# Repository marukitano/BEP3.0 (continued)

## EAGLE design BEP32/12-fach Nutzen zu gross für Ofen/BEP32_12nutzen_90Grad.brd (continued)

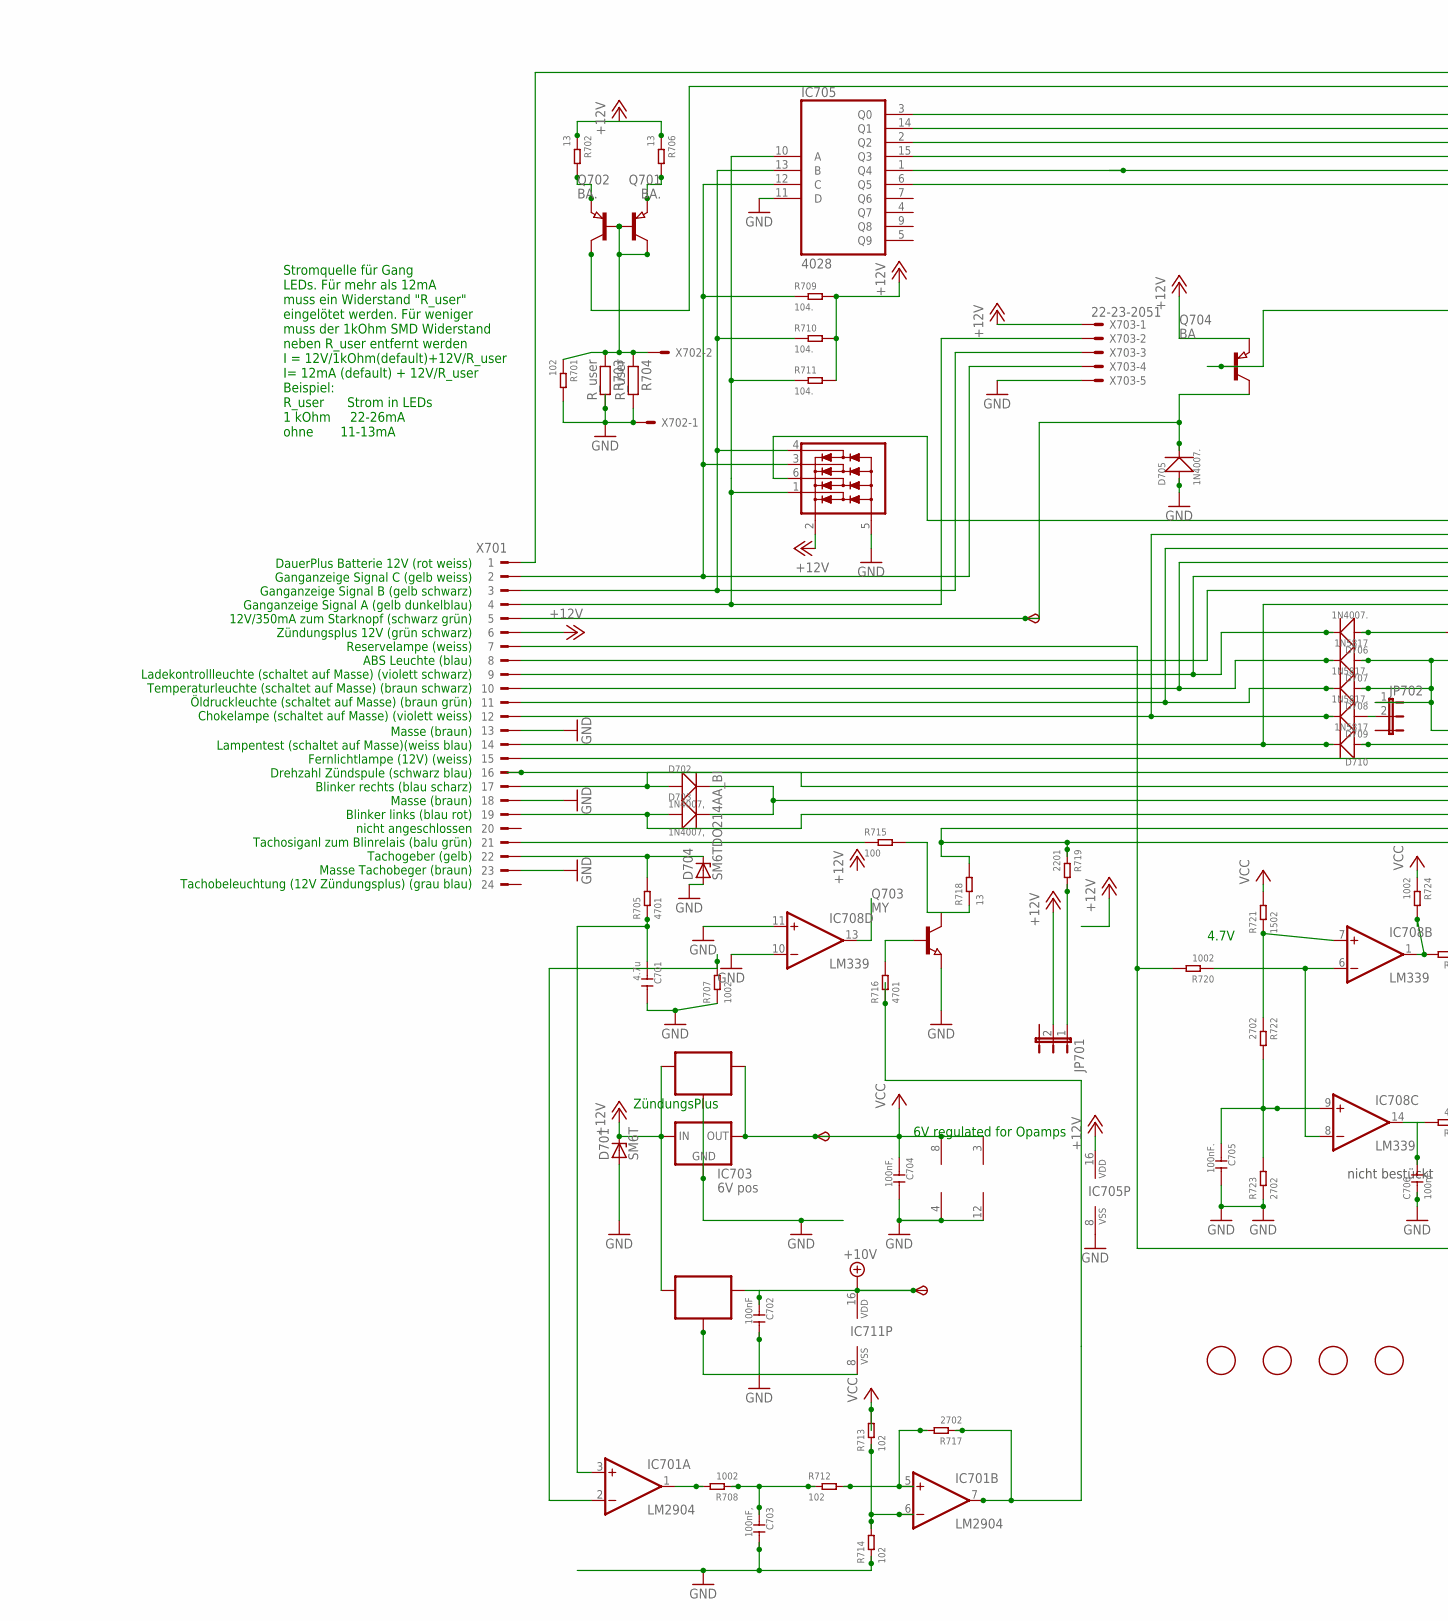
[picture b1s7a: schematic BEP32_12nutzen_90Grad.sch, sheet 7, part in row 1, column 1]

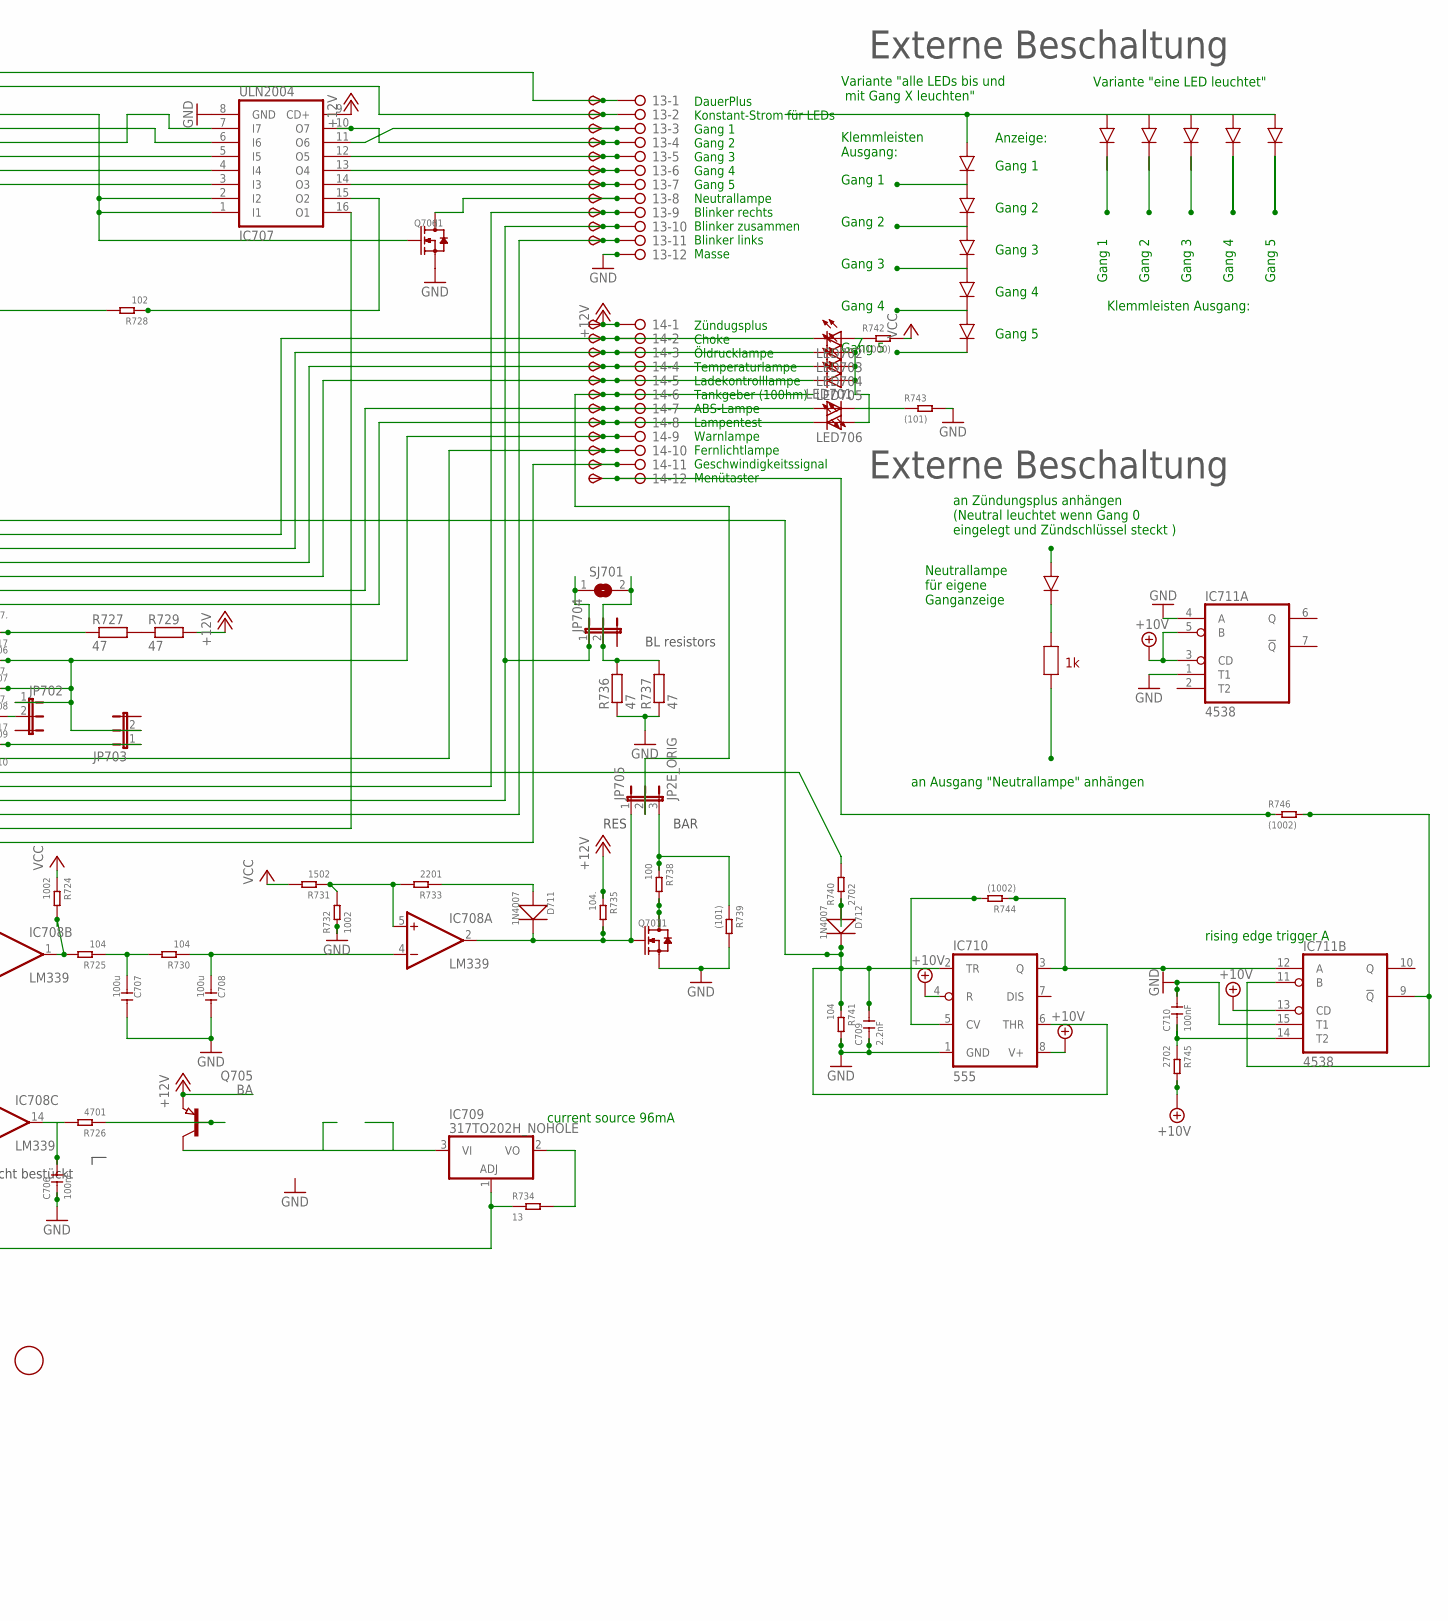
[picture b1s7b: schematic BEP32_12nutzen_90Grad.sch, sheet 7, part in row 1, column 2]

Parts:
6V701, 10V701: TPSB2.0; B2.0
13, 14: 2081-1132; 12-PIN
C701: 4.7u; C0805
C702, C710: 100nF; C0805
C703, C704: 100nF,; C0805
C705, C706: 100nF.; C0805
C707, C708: 100u; C1206
C709: 2.2nF; C0805
D701: SM6T; DO214AA
D702, D703: 1N4007,; DO-214AC
D704: SM6TDO214AA_BI; DO214AA_BI
D705, D706: 1N4007.; DO-214AC
D707, D710: 1N5817; DO-214AC_SLIM
D708, D709: 1N5817.; DO-214AC_SLIM
D711, D712: 1N4007; DO-214AC
FID701, FID702, FID703, FID704: FIDUCIAL; FIDUCIAL_1MM
IC701: LM2904; SO08
IC702: 78L06; SOT89_ROUND
IC703: 6V pos; 78LXX
IC704: 78L10; SOT89_ROUND
IC705: 4028; SO16
IC706: NUP4304SOT457_R; SOT457R_PHILIPS
IC707: ULN2004; SO16
IC708: LM339; SO14
IC709: 317TO202H_NOHOLE; TO220H_NOHOLE
IC710: 555; SO08
IC711: 4538; SO16
JP701, JP702, JP703, JP704: JP2EJP2_SMALLPADS; JP2_SMALLPADS
JP705: JP2E_ORIG; JP2_ORIG_SMALLPADS
LED701, LED702, LED703, LED704, LED705, LED706: LEDLD260; LD260
Q701, Q702: BA.; SOT89
Q703: MY; SOT89
Q704, Q705: BA; SOT89
Q706, Q707: J1; SOT-23
R701, R712, R713, R714, R728: 102; R0805
R702, R706, R718, R734: 13; R1206
R703, R704: R_user; R0805
R705, R716, R726: 4701; R0805
R707, R708, R720, R724, R732: 1002; R0805
R709, R710, R711, R735: 104.; R0805
R715, R738: 100; R0805
R717, R722, R723, R740, R745: 2702; R0805
R719, R733: 2201; R0805
R721, R731: 1502; R0805
R725, R730, R741: 104; R0805
R727, R729, R736, R737: 47; V235/17_1MM
R739, R743: (101); R0805
R742: (1000); R0805
R744, R746: (1002); R0805
SJ701: SJ
START701: TPSB2.0; B2.0
TP139, TP140, TP141, TP142, TP143, TP144, TP145, TP146, TP147, TP148, TP149, TP150, TP151, TP152, TP153, TP154, TP155, TP156, TP158, TP159, TP160, TP161: TPSB2.0; B2.0
TP157: TPSB1,27; B1,27
X701: CON_BMWV2; 24-PIN_V2
X702: 22-23-2021
X703: 22-23-2051

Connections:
+10V: 10V701.TP, C702.1, IC704.1 (OUT), IC710.4 (R), IC710.8 (V+), IC711.3 (CD), IC711.5 (B), IC711.13 (CD), IC711.16 (VDD), R745.2; also elsewhere on the board
+12V: 14.1, D701.C, IC702.3 (IN), IC703.IN, IC704.3 (IN), IC705.16 (VDD), IC706.2 (V+), IC707.9 (CD+), JP701.2, Q704.3 (E), Q705.3 (E), R702.1, R706.1, R709.2, R710.2, R711.2, R729.2, R735.1, TP160.TP, X701.6, X703.1; also elsewhere on the board
+12V7: IC701.7 (OUT), R716.1, R717.1
GND: 13.12, C701.2, C702.2, C703.2, C704.2, C705.2, C706.1, C707.2, C708.2, C709.1, C710.2, D701.A, D704.A, D705.1 (+), IC701.4 (V-), IC702.2 (GND), IC702.2@1 (GND), IC703.GND, IC704.2 (GND), IC704.2@1 (GND), IC705.8 (VSS), IC705.11 (D), IC706.5 (V-), IC707.8 (GND), IC708.10 (-IN), IC708.11 (+IN), IC708.12 (GND), IC710.1 (GND), IC711.1 (T1), IC711.4 (A), IC711.8 (VSS), IC711.15 (T1), Q703.3 (E), Q706.2 (S), Q707.2 (S), R701.2, R703.2, R704.2, R707.1, R714.1, R723.1, R732.1, R736.1, R737.1, R739.2, R741.2, R743.2, X701.13, X701.18, X701.23, X702.1, X703.5; also elsewhere on the board
unnamed: R727.2, R729.1
unnamed: 14.9, D707.1 (+), D708.1 (+), JP702.1, JP703.2, TP157.TP
unnamed: IC705.10 (A), IC706.1 (D1), R711.1, X701.4, X703.2
unnamed: IC705.13 (B), IC706.4 (D4), R710.1, X701.3, X703.3
unnamed: D705.2 (-), Q704.2 (C), START701.TP, X701.5
unnamed: IC705.12 (C), IC706.3 (D3), R709.1, X701.2, X703.4
unnamed: 14.7, LED701.A, TP155.TP, X701.8
unnamed: 14.2, D709.2 (-), LED702.K (C), TP150.TP, X701.12
unnamed: 14.3, D708.2 (-), LED703.K (C), TP151.TP, X701.11
unnamed: 14.4, D707.2 (-), LED704.K (C), TP152.TP, X701.10
unnamed: 14.8, D710.2 (-), LED706.K (C), TP156.TP, X701.14
unnamed: 13.9, D702.1 (+), TP147.TP, X701.17
unnamed: 13.11, D703.1 (+), TP149.TP, X701.19
unnamed: D704.C, R705.2, X701.22
unnamed: C701.1, IC701.3 (+IN), R705.1
unnamed: 14.11, IC707.16 (O1), R718.2, R719.1, TP159.TP
unnamed: IC708.1 (OUT), R724.2, R725.2
unnamed: C707.1, R725.1, R730.2
unnamed: C708.1, IC708.4 (-IN), R730.1
unnamed: IC708.5 (+IN), R731.1, R732.2, R733.2
unnamed: D711.1 (+), R733.1
unnamed: C705.1, IC708.9 (+IN), R722.2, R723.2
unnamed: C706.2, IC708.14 (OUT), R726.2
unnamed: Q705.1 (B), R726.1
unnamed: IC705.2 (Q2), IC707.7 (I7)
unnamed: 13.5, IC707.12 (O5), TP143.TP
unnamed: IC705.1 (Q4), IC707.4 (I4)
unnamed: 13.8, Q706.3 (D), TP146.TP
unnamed: 14.10, TP158.TP, X701.15
unnamed: 14.5, D706.2 (-), LED705.K (C), TP153.TP, X701.9
unnamed: D706.1 (+), R727.1
unnamed: IC705.6 (Q5), IC707.3 (I3)
unnamed: 13.4, IC707.10 (O7), TP142.TP
unnamed: IC709.1 (ADJ), R720.2, R734.1, X701.7
unnamed: IC708.6 (-IN), IC708.8 (-IN), R720.1
unnamed: 13.2, Q701.2 (C), TP140.TP
unnamed: 13.1, TP139.TP, X701.1
unnamed: R740.2, X701.16
unnamed: IC705.15 (Q3), IC707.5 (I5)
unnamed: 13.6, IC707.13 (O4), TP144.TP
unnamed: 13.7, IC707.14 (O3), TP145.TP
unnamed: 14.6, JP705.2, TP154.TP
unnamed: LED701.K (C), R743.1
unnamed: LED702.A, LED703.A, LED704.A, LED705.A, LED706.A, R742.1
unnamed: Q704.1 (B), R728.2
unnamed: IC705.3 (Q0), IC707.1 (I1), IC707.2 (I2), Q706.1 (G)
unnamed: IC705.14 (Q1), IC707.6 (I6)
unnamed: 13.3, IC707.11 (O6), TP141.TP
unnamed: Q701.1 (B), Q702.1 (B), Q702.2 (C), R701.1, R703.1, R704.1, X702.2
unnamed: Q701.3 (E), R702.2
unnamed: Q702.3 (E), R706.2
unnamed: IC708.7 (+IN), R721.1, R722.1
unnamed: IC701.2 (-IN), R707.2
unnamed: Q703.1 (B), R716.2
unnamed: Q707.3 (D), R738.2
unnamed: IC709.2 (VO), R734.2
unnamed: IC709.3 (VI), Q705.2 (C)
unnamed: C709.2, D712.2 (-), IC706.6 (D2), IC710.2 (TR), IC710.6 (THR), R741.1
unnamed: IC710.5 (CV), R744.2
unnamed: IC710.3 (Q), IC711.12 (A), R744.1
unnamed: D712.1 (+), R740.1
unnamed: 13.10, D702.2 (-), D703.2 (-), JP704.1, SJ701.1, TP148.TP
unnamed: JP704.2, R736.2, R737.2, SJ701.2
unnamed: IC711.9 (!Q), IC711.11 (B), R746.2
unnamed: C710.1, IC711.14 (T2), R745.1
unnamed: JP701.1, R719.2
unnamed: IC707.15 (O2), R728.1
unnamed: 14.12, R746.1, TP161.TP
unnamed: D709.1 (+), JP702.2
unnamed: D711.2 (-), IC708.2 (OUT), JP705.1, Q707.1 (G), R735.2
unnamed: IC701.1 (OUT), R708.2
unnamed: C703.1, R708.1, R712.1
unnamed: IC701.5 (+IN), R712.2, R717.2
unnamed: IC701.6 (-IN), R713.1, R714.2
unnamed: D710.1 (+), JP703.1
unnamed: JP705.3, R738.1, R739.1
unnamed: R715.1, X701.21
unnamed: Q703.2 (C), R715.2, R718.1
VCC: 6V701.TP, C704.1, IC701.8 (V+), IC702.1 (OUT), IC703.OUT, IC708.3 (V+), R713.2, R721.2, R724.1, R731.2, R742.2; also elsewhere on the board

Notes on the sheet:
6V regulated for Opamps
current source 96mA
ZündungsPlus
Zündugsplus Choke Öldrucklampe Temperaturlampe Ladekontrolllampe Tankgeber (100hm) ABS-Lampe Lampentest Warnlampe Fernlichtlampe Geschwindigkeitssignal Menütaster
DauerPlus Konstant-Strom für LEDs Gang 1 Gang 2 Gang 3 Gang 4 Gang 5 Neutrallampe Blinker rechts Blinker zusammen Blinker links Masse
DauerPlus Batterie 12V (rot weiss) Ganganzeige Signal C (gelb weiss) Ganganzeige Signal B (gelb schwarz) Ganganzeige Signal A (gelb dunkelblau) 12V/350mA zum Starknopf (schwarz grün) Zündungsplus 12V (grün schwarz) Reservelampe (weiss) ABS Leuchte (blau) Ladekontrollleuchte (schaltet auf Masse) (vi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
Masse (braun) Lampentest (schaltet auf Masse)(weiss blau) Fernlichtlampe (12V) (weiss) Drehzahl Zündspule (schwarz blau) Blinker rechts (blau scharz) Masse (braun) Blinker links (blau rot) nicht angeschlossen Tachosiganl zum Blinrelais (balu grün) Tachogeber (gelb) Masse Tachobeger (braun) Tachobel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
4.7V
Stromquelle für Gang LEDs. Für mehr als 12mA muss ein Widerstand "R_user" eingelötet werden. Für weniger muss der 1kOhm SMD Widerstand neben R_user entfernt werden I = 12V/1kOhm(default)+12V/R_user I= 12mA (default) + 12V/R_user Beispiel: R_user Strom in LEDs 1 kOhm 22-26mA ohne 11-13mA
Gang 1
Gang 2
Gang 3
Gang 4
Gang 5
Variante "eine LED leuchtet"
Variante "alle LEDs bis und mit Gang X leuchten"
Klemmleisten Ausgang:
Klemmleisten Ausgang:
an Zündungsplus anhängen (Neutral leuchtet wenn Gang 0 eingelegt und Zündschlüssel steckt )
an Ausgang "Neutrallampe" anhängen
Neutrallampe für eigene Ganganzeige
Externe Beschaltung
Anzeige:
nicht bestückt
rising edge trigger A
BAR
RES
BL resistors

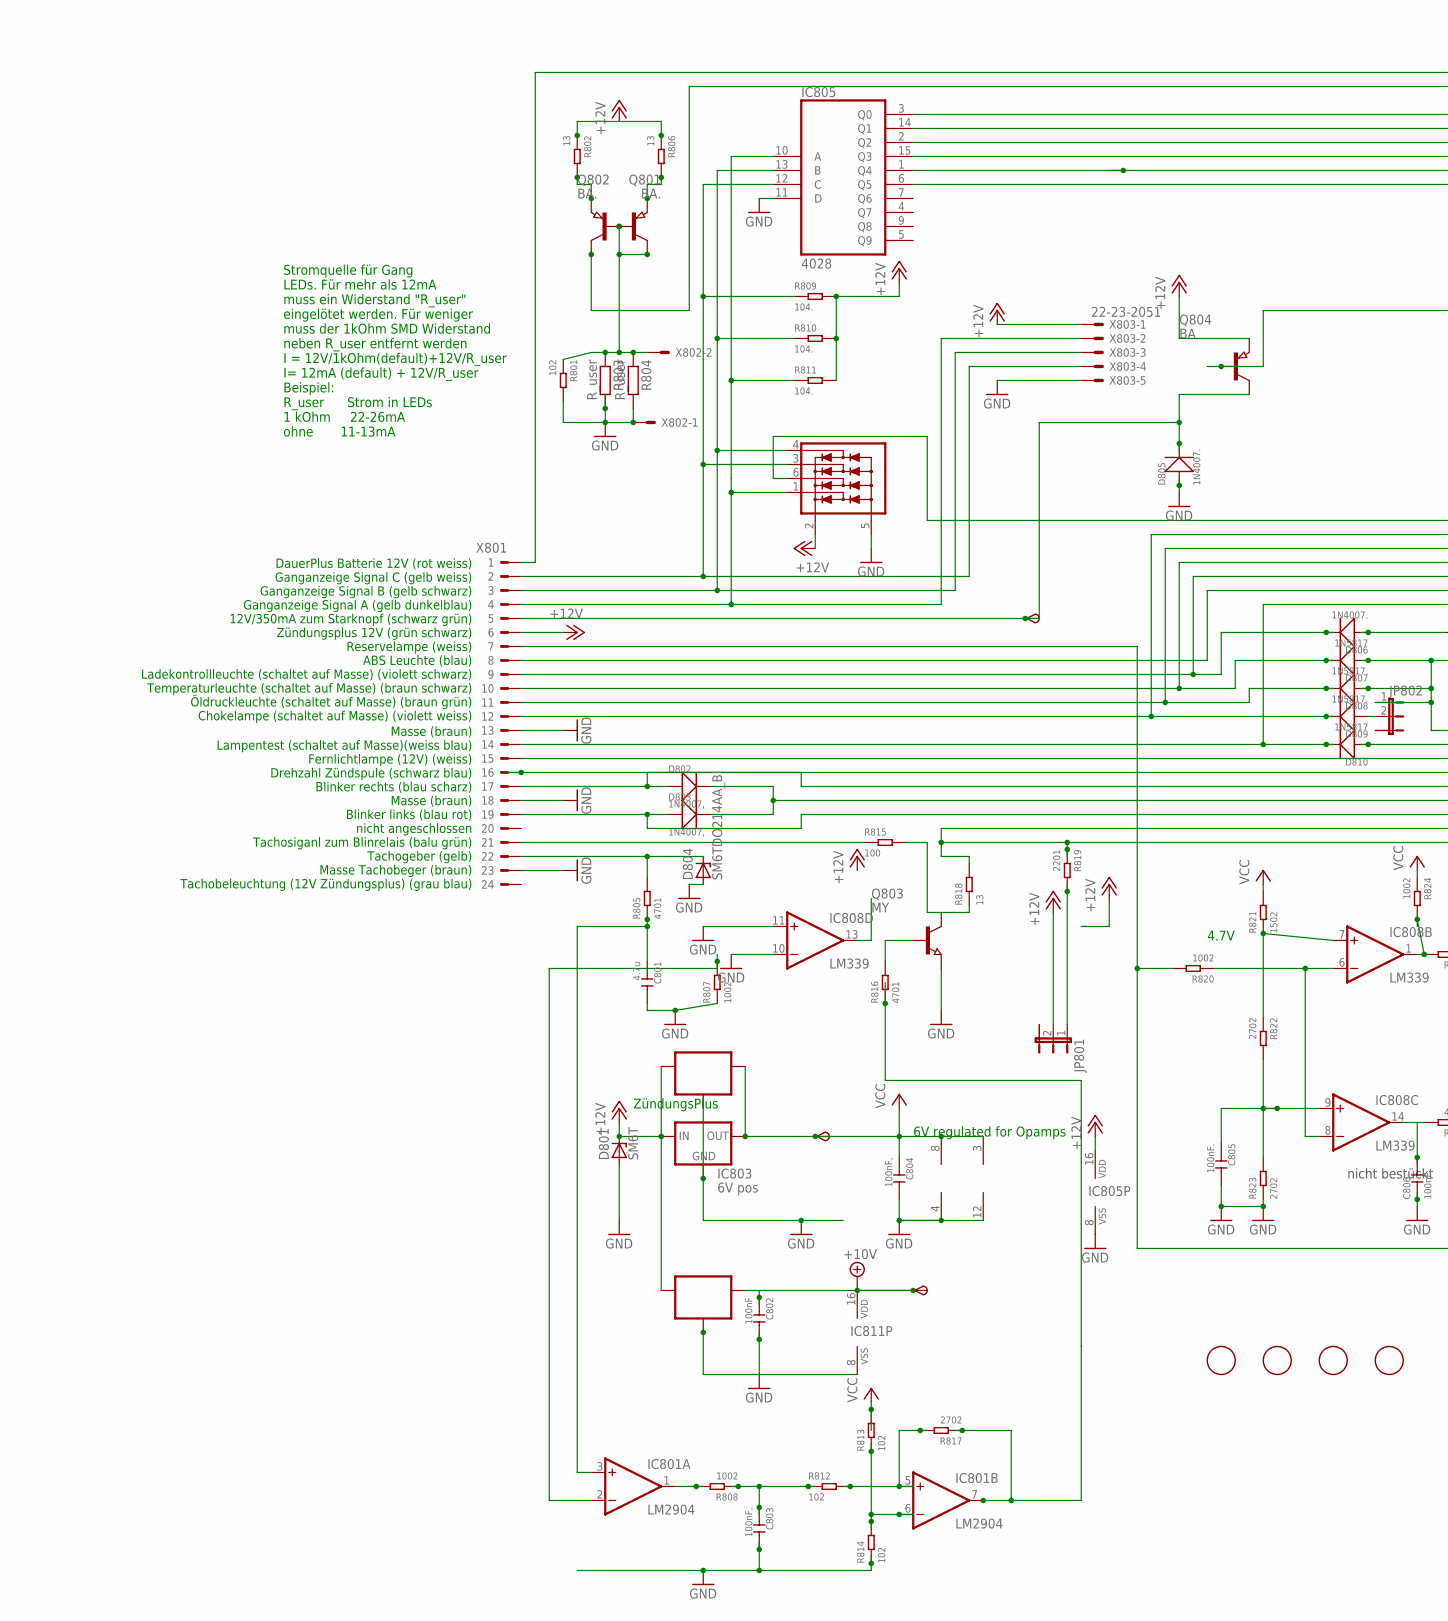
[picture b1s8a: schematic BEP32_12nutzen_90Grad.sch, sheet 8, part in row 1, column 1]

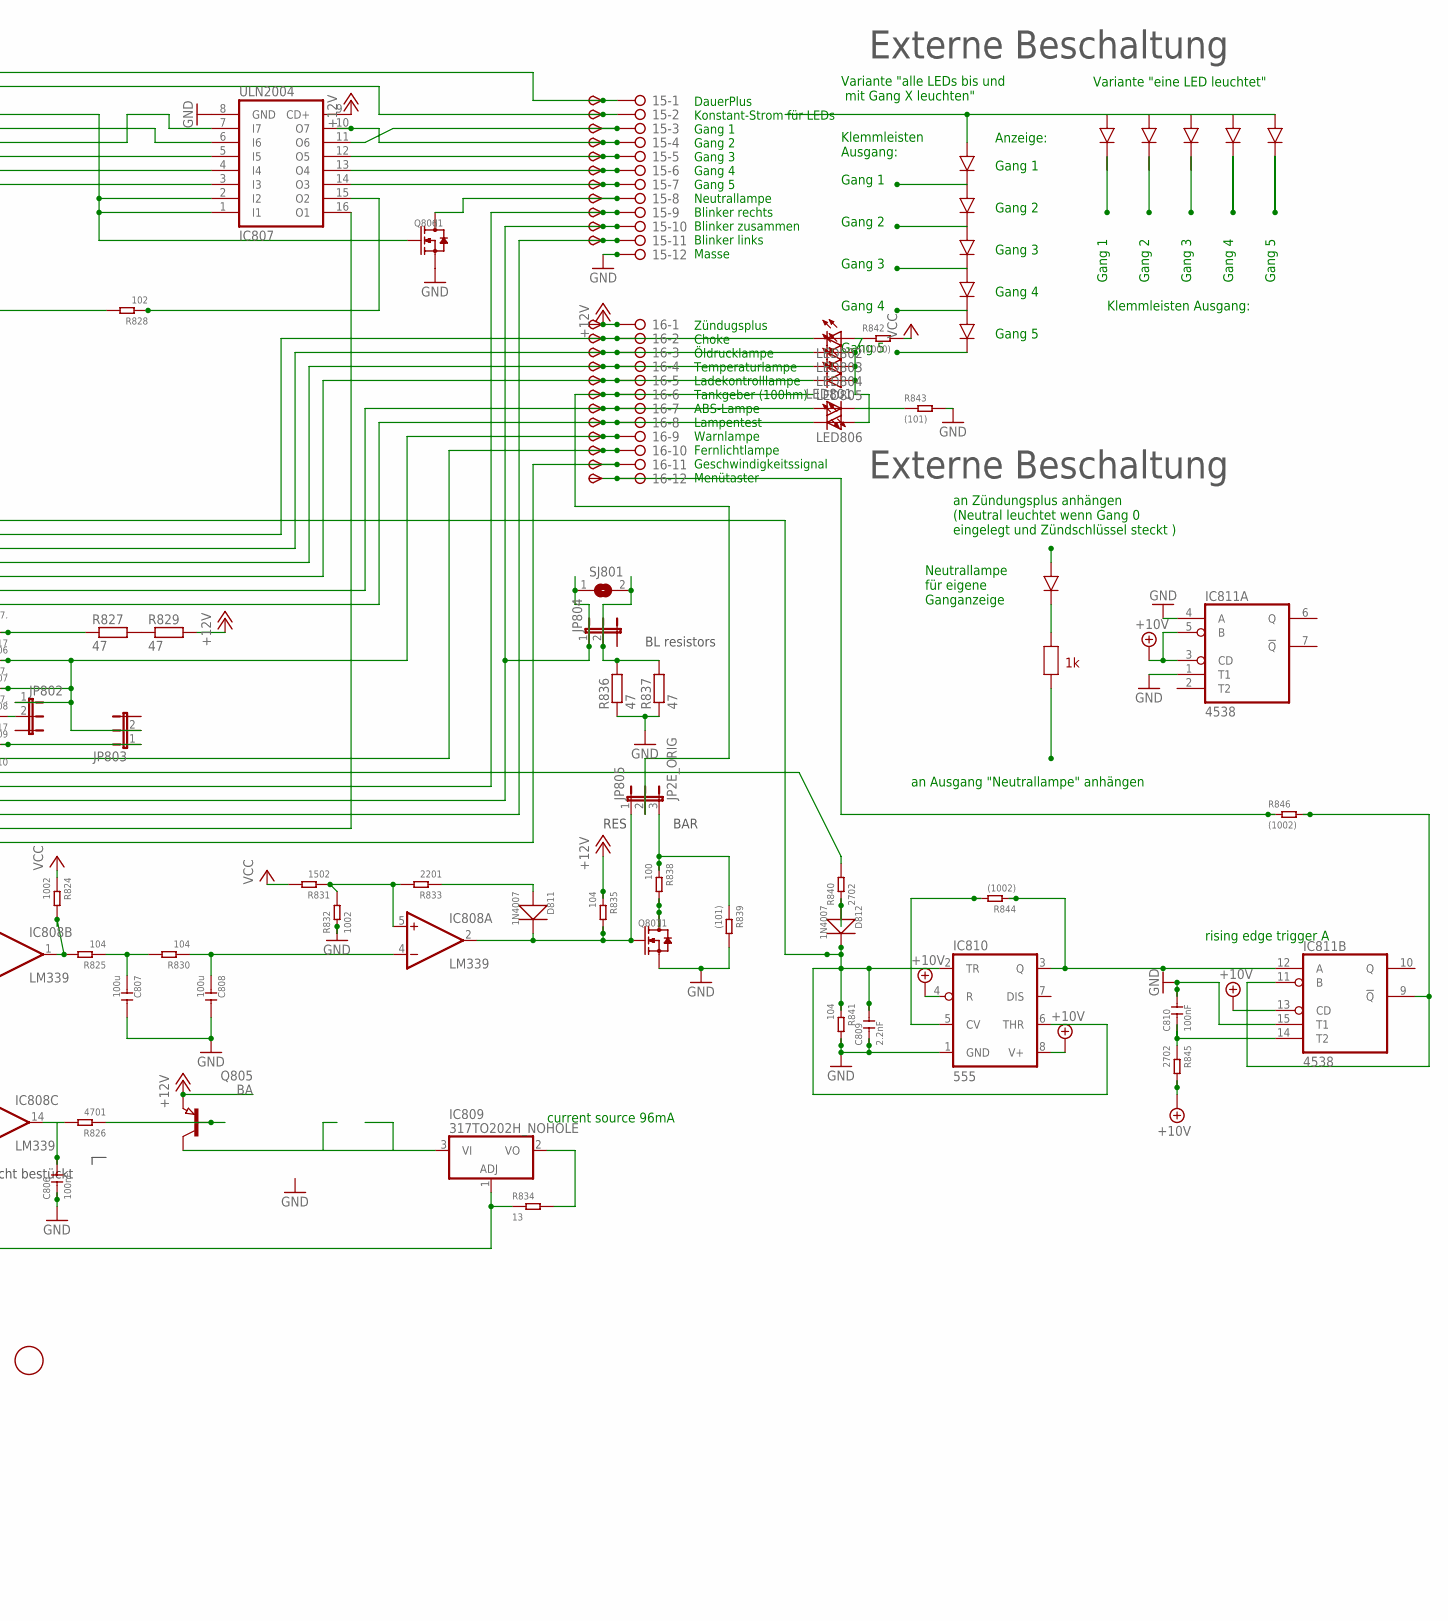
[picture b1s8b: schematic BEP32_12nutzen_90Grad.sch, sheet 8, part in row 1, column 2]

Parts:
6V801, 10V801: TPSB2.0; B2.0
15, 16: 2081-1132; 12-PIN
C801: 4.7u; C0805
C802, C810: 100nF; C0805
C803, C804: 100nF,; C0805
C805, C806: 100nF.; C0805
C807, C808: 100u; C1206
C809: 2.2nF; C0805
D801: SM6T; DO214AA
D802, D803: 1N4007,; DO-214AC
D804: SM6TDO214AA_BI; DO214AA_BI
D805, D806: 1N4007.; DO-214AC
D807, D810: 1N5817; DO-214AC_SLIM
D808, D809: 1N5817.; DO-214AC_SLIM
D811, D812: 1N4007; DO-214AC
FID801, FID802, FID803, FID804: FIDUCIAL; FIDUCIAL_1MM
IC801: LM2904; SO08
IC802: 78L06; SOT89_ROUND
IC803: 6V pos; 78LXX
IC804: 78L10; SOT89_ROUND
IC805: 4028; SO16
IC806: NUP4304SOT457_R; SOT457R_PHILIPS
IC807: ULN2004; SO16
IC808: LM339; SO14
IC809: 317TO202H_NOHOLE; TO220H_NOHOLE
IC810: 555; SO08
IC811: 4538; SO16
JP801, JP802, JP803, JP804: JP2EJP2_SMALLPADS; JP2_SMALLPADS
JP805: JP2E_ORIG; JP2_ORIG_SMALLPADS
LED801, LED802, LED803, LED804, LED805, LED806: LEDLD260; LD260
Q801, Q802: BA.; SOT89
Q803: MY; SOT89
Q804, Q805: BA; SOT89
Q806, Q807: J1; SOT-23
R801, R812, R813, R814, R828: 102; R0805
R802, R806, R818, R834: 13; R1206
R803, R804: R_user; R0805
R805, R816, R826: 4701; R0805
R807, R808, R820, R824, R832: 1002; R0805
R809, R810, R811: 104.; R0805
R815, R838: 100; R0805
R817, R822, R823, R840, R845: 2702; R0805
R819, R833: 2201; R0805
R821, R831: 1502; R0805
R825, R830, R835, R841: 104; R0805
R827, R829, R836, R837: 47; V235/17_1MM
R839, R843: (101); R0805
R842: (1000); R0805
R844, R846: (1002); R0805
SJ801: SJ
START801: TPSB2.0; B2.0
TP162, TP163, TP164, TP165, TP166, TP167, TP168, TP169, TP170, TP171, TP172, TP173, TP174, TP175, TP176, TP177, TP178, TP179, TP181, TP182, TP183, TP184: TPSB2.0; B2.0
TP180: TPSB1,27; B1,27
X801: CON_BMWV2; 24-PIN_V2
X802: 22-23-2021
X803: 22-23-2051

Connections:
+10V: 10V801.TP, C802.1, IC804.1 (OUT), IC810.4 (R), IC810.8 (V+), IC811.3 (CD), IC811.5 (B), IC811.13 (CD), IC811.16 (VDD), R845.2; also elsewhere on the board
+12V: 16.1, D801.C, IC802.3 (IN), IC803.IN, IC804.3 (IN), IC805.16 (VDD), IC806.2 (V+), IC807.9 (CD+), JP801.2, Q804.3 (E), Q805.3 (E), R802.1, R806.1, R809.2, R810.2, R811.2, R829.2, R835.1, TP183.TP, X801.6, X803.1; also elsewhere on the board
+12V8: IC801.7 (OUT), R816.1, R817.1
GND: 15.12, C801.2, C802.2, C803.2, C804.2, C805.2, C806.1, C807.2, C808.2, C809.1, C810.2, D801.A, D804.A, D805.1 (+), IC801.4 (V-), IC802.2 (GND), IC802.2@1 (GND), IC803.GND, IC804.2 (GND), IC804.2@1 (GND), IC805.8 (VSS), IC805.11 (D), IC806.5 (V-), IC807.8 (GND), IC808.10 (-IN), IC808.11 (+IN), IC808.12 (GND), IC810.1 (GND), IC811.1 (T1), IC811.4 (A), IC811.8 (VSS), IC811.15 (T1), Q803.3 (E), Q806.2 (S), Q807.2 (S), R801.2, R803.2, R804.2, R807.1, R814.1, R823.1, R832.1, R836.1, R837.1, R839.2, R841.2, R843.2, X801.13, X801.18, X801.23, X802.1, X803.5; also elsewhere on the board
unnamed: R827.2, R829.1
unnamed: 16.9, D807.1 (+), D808.1 (+), JP802.1, JP803.2, TP180.TP
unnamed: IC805.10 (A), IC806.1 (D1), R811.1, X801.4, X803.2
unnamed: IC805.13 (B), IC806.4 (D4), R810.1, X801.3, X803.3
unnamed: D805.2 (-), Q804.2 (C), START801.TP, X801.5
unnamed: IC805.12 (C), IC806.3 (D3), R809.1, X801.2, X803.4
unnamed: 16.7, LED801.A, TP178.TP, X801.8
unnamed: 16.2, D809.2 (-), LED802.K (C), TP173.TP, X801.12
unnamed: 16.3, D808.2 (-), LED803.K (C), TP174.TP, X801.11
unnamed: 16.4, D807.2 (-), LED804.K (C), TP175.TP, X801.10
unnamed: 16.8, D810.2 (-), LED806.K (C), TP179.TP, X801.14
unnamed: 15.9, D802.1 (+), TP170.TP, X801.17
unnamed: 15.11, D803.1 (+), TP172.TP, X801.19
unnamed: D804.C, R805.2, X801.22
unnamed: C801.1, IC801.3 (+IN), R805.1
unnamed: 16.11, IC807.16 (O1), R818.2, R819.1, TP182.TP
unnamed: IC808.1 (OUT), R824.2, R825.2
unnamed: C807.1, R825.1, R830.2
unnamed: C808.1, IC808.4 (-IN), R830.1
unnamed: IC808.5 (+IN), R831.1, R832.2, R833.2
unnamed: D811.1 (+), R833.1
unnamed: C805.1, IC808.9 (+IN), R822.2, R823.2
unnamed: C806.2, IC808.14 (OUT), R826.2
unnamed: Q805.1 (B), R826.1
unnamed: IC805.2 (Q2), IC807.7 (I7)
unnamed: 15.5, IC807.12 (O5), TP166.TP
unnamed: IC805.1 (Q4), IC807.4 (I4)
unnamed: 15.8, Q806.3 (D), TP169.TP
unnamed: 16.10, TP181.TP, X801.15
unnamed: 16.5, D806.2 (-), LED805.K (C), TP176.TP, X801.9
unnamed: D806.1 (+), R827.1
unnamed: IC805.6 (Q5), IC807.3 (I3)
unnamed: 15.4, IC807.10 (O7), TP165.TP
unnamed: IC809.1 (ADJ), R820.2, R834.1, X801.7
unnamed: IC808.6 (-IN), IC808.8 (-IN), R820.1
unnamed: 15.2, Q801.2 (C), TP163.TP
unnamed: 15.1, TP162.TP, X801.1
unnamed: R840.2, X801.16
unnamed: IC805.15 (Q3), IC807.5 (I5)
unnamed: 15.6, IC807.13 (O4), TP167.TP
unnamed: 15.7, IC807.14 (O3), TP168.TP
unnamed: 16.6, JP805.2, TP177.TP
unnamed: LED801.K (C), R843.1
unnamed: LED802.A, LED803.A, LED804.A, LED805.A, LED806.A, R842.1
unnamed: Q804.1 (B), R828.2
unnamed: IC805.3 (Q0), IC807.1 (I1), IC807.2 (I2), Q806.1 (G)
unnamed: IC805.14 (Q1), IC807.6 (I6)
unnamed: 15.3, IC807.11 (O6), TP164.TP
unnamed: Q801.1 (B), Q802.1 (B), Q802.2 (C), R801.1, R803.1, R804.1, X802.2
unnamed: Q801.3 (E), R802.2
unnamed: Q802.3 (E), R806.2
unnamed: IC808.7 (+IN), R821.1, R822.1
unnamed: IC801.2 (-IN), R807.2
unnamed: Q803.1 (B), R816.2
unnamed: Q807.3 (D), R838.2
unnamed: IC809.2 (VO), R834.2
unnamed: IC809.3 (VI), Q805.2 (C)
unnamed: C809.2, D812.2 (-), IC806.6 (D2), IC810.2 (TR), IC810.6 (THR), R841.1
unnamed: IC810.5 (CV), R844.2
unnamed: IC810.3 (Q), IC811.12 (A), R844.1
unnamed: D812.1 (+), R840.1
unnamed: 15.10, D802.2 (-), D803.2 (-), JP804.1, SJ801.1, TP171.TP
unnamed: JP804.2, R836.2, R837.2, SJ801.2
unnamed: IC811.9 (!Q), IC811.11 (B), R846.2
unnamed: C810.1, IC811.14 (T2), R845.1
unnamed: JP801.1, R819.2
unnamed: IC807.15 (O2), R828.1
unnamed: 16.12, R846.1, TP184.TP
unnamed: D809.1 (+), JP802.2
unnamed: D811.2 (-), IC808.2 (OUT), JP805.1, Q807.1 (G), R835.2
unnamed: IC801.1 (OUT), R808.2
unnamed: C803.1, R808.1, R812.1
unnamed: IC801.5 (+IN), R812.2, R817.2
unnamed: IC801.6 (-IN), R813.1, R814.2
unnamed: D810.1 (+), JP803.1
unnamed: JP805.3, R838.1, R839.1
unnamed: R815.1, X801.21
unnamed: Q803.2 (C), R815.2, R818.1
VCC: 6V801.TP, C804.1, IC801.8 (V+), IC802.1 (OUT), IC803.OUT, IC808.3 (V+), R813.2, R821.2, R824.1, R831.2, R842.2; also elsewhere on the board

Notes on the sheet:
6V regulated for Opamps
current source 96mA
ZündungsPlus
Zündugsplus Choke Öldrucklampe Temperaturlampe Ladekontrolllampe Tankgeber (100hm) ABS-Lampe Lampentest Warnlampe Fernlichtlampe Geschwindigkeitssignal Menütaster
DauerPlus Konstant-Strom für LEDs Gang 1 Gang 2 Gang 3 Gang 4 Gang 5 Neutrallampe Blinker rechts Blinker zusammen Blinker links Masse
DauerPlus Batterie 12V (rot weiss) Ganganzeige Signal C (gelb weiss) Ganganzeige Signal B (gelb schwarz) Ganganzeige Signal A (gelb dunkelblau) 12V/350mA zum Starknopf (schwarz grün) Zündungsplus 12V (grün schwarz) Reservelampe (weiss) ABS Leuchte (blau) Ladekontrollleuchte (schaltet auf Masse) (vi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
Masse (braun) Lampentest (schaltet auf Masse)(weiss blau) Fernlichtlampe (12V) (weiss) Drehzahl Zündspule (schwarz blau) Blinker rechts (blau scharz) Masse (braun) Blinker links (blau rot) nicht angeschlossen Tachosiganl zum Blinrelais (balu grün) Tachogeber (gelb) Masse Tachobeger (braun) Tachobel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
4.7V
Stromquelle für Gang LEDs. Für mehr als 12mA muss ein Widerstand "R_user" eingelötet werden. Für weniger muss der 1kOhm SMD Widerstand neben R_user entfernt werden I = 12V/1kOhm(default)+12V/R_user I= 12mA (default) + 12V/R_user Beispiel: R_user Strom in LEDs 1 kOhm 22-26mA ohne 11-13mA
Gang 1
Gang 2
Gang 3
Gang 4
Gang 5
Variante "eine LED leuchtet"
Variante "alle LEDs bis und mit Gang X leuchten"
Klemmleisten Ausgang:
Klemmleisten Ausgang:
an Zündungsplus anhängen (Neutral leuchtet wenn Gang 0 eingelegt und Zündschlüssel steckt )
an Ausgang "Neutrallampe" anhängen
Neutrallampe für eigene Ganganzeige
Externe Beschaltung
Anzeige:
nicht bestückt
rising edge trigger A
BAR
RES
BL resistors

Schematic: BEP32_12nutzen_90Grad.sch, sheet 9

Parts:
6V901, 10V901: TPSB2.0; B2.0
17, 18: 2081-1132; 12-PIN
C901: 4.7u; C0805
C902, C910: 100nF; C0805
C903, C904: 100nF,; C0805
C905, C906: 100nF.; C0805
C907, C908: 100u; C1206
C909: 2.2nF; C0805
D901: SM6T; DO214AA
D902, D903: 1N4007,; DO-214AC
D904: SM6TDO214AA_BI; DO214AA_BI
D905, D906: 1N4007.; DO-214AC
D907, D910: 1N5817; DO-214AC_SLIM
D908, D909: 1N5817.; DO-214AC_SLIM
D911, D912: 1N4007; DO-214AC
FID901, FID902, FID903, FID904: FIDUCIAL; FIDUCIAL_1MM
IC901: LM2904; SO08
IC902: 78L06; SOT89_ROUND
IC903: 6V pos; 78LXX
IC904: 78L10; SOT89_ROUND
IC905: 4028; SO16
IC906: NUP4304SOT457_R; SOT457R_PHILIPS
IC907: ULN2004; SO16
IC908: LM339; SO14
IC909: 317TO202H_NOHOLE; TO220H_NOHOLE
IC910: 555; SO08
IC911: 4538; SO16
JP901, JP902, JP903, JP904: JP2EJP2_SMALLPADS; JP2_SMALLPADS
JP905: JP2E_ORIG; JP2_ORIG_SMALLPADS
LED901, LED902, LED903, LED904, LED905, LED906: LEDLD260; LD260
Q901, Q902: BA.; SOT89
Q903: MY; SOT89
Q904, Q905: BA; SOT89
Q906, Q907: J1; SOT-23
R901, R912, R913, R914, R928: 102; R0805
R902, R906, R918, R934: 13; R1206
R903, R904: R_user; R0805
R905, R916, R926: 4701; R0805
R907, R908, R920, R924, R932: 1002; R0805
R909, R910, R911, R935: 104.; R0805
R915, R938: 100; R0805
R917, R922, R923, R940, R945: 2702; R0805
R919, R933: 2201; R0805
R921, R931: 1502; R0805
R925, R930, R941: 104; R0805
R927, R929, R936, R937: 47; V235/17_1MM
R939, R943: (101); R0805
R942: (1000); R0805
R944, R946: (1002); R0805
SJ901: SJ
START901: TPSB2.0; B2.0
TP185, TP186, TP187, TP188, TP189, TP190, TP191, TP192, TP193, TP194, TP195, TP196, TP197, TP198, TP199, TP200, TP201, TP202, TP204, TP205, TP206, TP207: TPSB2.0; B2.0
TP203: TPSB1,27; B1,27
X901: CON_BMWV2; 24-PIN_V2
X902: 22-23-2021
X903: 22-23-2051

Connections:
+10V: 10V901.TP, C902.1, IC904.1 (OUT), IC910.4 (R), IC910.8 (V+), IC911.3 (CD), IC911.5 (B), IC911.13 (CD), IC911.16 (VDD), R945.2; also elsewhere on the board
+12V: 18.1, D901.C, IC902.3 (IN), IC903.IN, IC904.3 (IN), IC905.16 (VDD), IC906.2 (V+), IC907.9 (CD+), JP901.2, Q904.3 (E), Q905.3 (E), R902.1, R906.1, R909.2, R910.2, R911.2, R929.2, R935.1, TP206.TP, X901.6, X903.1; also elsewhere on the board
+12V9: IC901.7 (OUT), R916.1, R917.1
GND: 17.12, C901.2, C902.2, C903.2, C904.2, C905.2, C906.1, C907.2, C908.2, C909.1, C910.2, D901.A, D904.A, D905.1 (+), IC901.4 (V-), IC902.2 (GND), IC902.2@1 (GND), IC903.GND, IC904.2 (GND), IC904.2@1 (GND), IC905.8 (VSS), IC905.11 (D), IC906.5 (V-), IC907.8 (GND), IC908.10 (-IN), IC908.11 (+IN), IC908.12 (GND), IC910.1 (GND), IC911.1 (T1), IC911.4 (A), IC911.8 (VSS), IC911.15 (T1), Q903.3 (E), Q906.2 (S), Q907.2 (S), R901.2, R903.2, R904.2, R907.1, R914.1, R923.1, R932.1, R936.1, R937.1, R939.2, R941.2, R943.2, X901.13, X901.18, X901.23, X902.1, X903.5; also elsewhere on the board
unnamed: R927.2, R929.1
unnamed: 18.9, D907.1 (+), D908.1 (+), JP902.1, JP903.2, TP203.TP
unnamed: IC905.10 (A), IC906.1 (D1), R911.1, X901.4, X903.2
unnamed: IC905.13 (B), IC906.4 (D4), R910.1, X901.3, X903.3
unnamed: D905.2 (-), Q904.2 (C), START901.TP, X901.5
unnamed: IC905.12 (C), IC906.3 (D3), R909.1, X901.2, X903.4
unnamed: 18.7, LED901.A, TP201.TP, X901.8
unnamed: 18.2, D909.2 (-), LED902.K (C), TP196.TP, X901.12
unnamed: 18.3, D908.2 (-), LED903.K (C), TP197.TP, X901.11
unnamed: 18.4, D907.2 (-), LED904.K (C), TP198.TP, X901.10
unnamed: 18.8, D910.2 (-), LED906.K (C), TP202.TP, X901.14
unnamed: 17.9, D902.1 (+), TP193.TP, X901.17
unnamed: 17.11, D903.1 (+), TP195.TP, X901.19
unnamed: D904.C, R905.2, X901.22
unnamed: C901.1, IC901.3 (+IN), R905.1
unnamed: 18.11, IC907.16 (O1), R918.2, R919.1, TP205.TP
unnamed: IC908.1 (OUT), R924.2, R925.2
unnamed: C907.1, R925.1, R930.2
unnamed: C908.1, IC908.4 (-IN), R930.1
unnamed: IC908.5 (+IN), R931.1, R932.2, R933.2
unnamed: D911.1 (+), R933.1
unnamed: C905.1, IC908.9 (+IN), R922.2, R923.2
unnamed: C906.2, IC908.14 (OUT), R926.2
unnamed: Q905.1 (B), R926.1
unnamed: IC905.2 (Q2), IC907.7 (I7)
unnamed: 17.5, IC907.12 (O5), TP189.TP
unnamed: IC905.1 (Q4), IC907.4 (I4)
unnamed: 17.8, Q906.3 (D), TP192.TP
unnamed: 18.10, TP204.TP, X901.15
unnamed: 18.5, D906.2 (-), LED905.K (C), TP199.TP, X901.9
unnamed: D906.1 (+), R927.1
unnamed: IC905.6 (Q5), IC907.3 (I3)
unnamed: 17.4, IC907.10 (O7), TP188.TP
unnamed: IC909.1 (ADJ), R920.2, R934.1, X901.7
unnamed: IC908.6 (-IN), IC908.8 (-IN), R920.1
unnamed: 17.2, Q901.2 (C), TP186.TP
unnamed: 17.1, TP185.TP, X901.1
unnamed: R940.2, X901.16
unnamed: IC905.15 (Q3), IC907.5 (I5)
unnamed: 17.6, IC907.13 (O4), TP190.TP
unnamed: 17.7, IC907.14 (O3), TP191.TP
unnamed: 18.6, JP905.2, TP200.TP
unnamed: LED901.K (C), R943.1
unnamed: LED902.A, LED903.A, LED904.A, LED905.A, LED906.A, R942.1
unnamed: Q904.1 (B), R928.2
unnamed: IC905.3 (Q0), IC907.1 (I1), IC907.2 (I2), Q906.1 (G)
unnamed: IC905.14 (Q1), IC907.6 (I6)
unnamed: 17.3, IC907.11 (O6), TP187.TP
unnamed: Q901.1 (B), Q902.1 (B), Q902.2 (C), R901.1, R903.1, R904.1, X902.2
unnamed: Q901.3 (E), R902.2
unnamed: Q902.3 (E), R906.2
unnamed: IC908.7 (+IN), R921.1, R922.1
unnamed: IC901.2 (-IN), R907.2
unnamed: Q903.1 (B), R916.2
unnamed: Q907.3 (D), R938.2
unnamed: IC909.2 (VO), R934.2
unnamed: IC909.3 (VI), Q905.2 (C)
unnamed: C909.2, D912.2 (-), IC906.6 (D2), IC910.2 (TR), IC910.6 (THR), R941.1
unnamed: IC910.5 (CV), R944.2
unnamed: IC910.3 (Q), IC911.12 (A), R944.1
unnamed: D912.1 (+), R940.1
unnamed: 17.10, D902.2 (-), D903.2 (-), JP904.1, SJ901.1, TP194.TP
unnamed: JP904.2, R936.2, R937.2, SJ901.2
unnamed: IC911.9 (!Q), IC911.11 (B), R946.2
unnamed: C910.1, IC911.14 (T2), R945.1
unnamed: JP901.1, R919.2
unnamed: IC907.15 (O2), R928.1
unnamed: 18.12, R946.1, TP207.TP
unnamed: D909.1 (+), JP902.2
unnamed: D911.2 (-), IC908.2 (OUT), JP905.1, Q907.1 (G), R935.2
unnamed: IC901.1 (OUT), R908.2
unnamed: C903.1, R908.1, R912.1
unnamed: IC901.5 (+IN), R912.2, R917.2
unnamed: IC901.6 (-IN), R913.1, R914.2
unnamed: D910.1 (+), JP903.1
unnamed: JP905.3, R938.1, R939.1
unnamed: R915.1, X901.21
unnamed: Q903.2 (C), R915.2, R918.1
VCC: 6V901.TP, C904.1, IC901.8 (V+), IC902.1 (OUT), IC903.OUT, IC908.3 (V+), R913.2, R921.2, R924.1, R931.2, R942.2; also elsewhere on the board

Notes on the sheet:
6V regulated for Opamps
current source 96mA
ZündungsPlus
Zündugsplus Choke Öldrucklampe Temperaturlampe Ladekontrolllampe Tankgeber (100hm) ABS-Lampe Lampentest Warnlampe Fernlichtlampe Geschwindigkeitssignal Menütaster
DauerPlus Konstant-Strom für LEDs Gang 1 Gang 2 Gang 3 Gang 4 Gang 5 Neutrallampe Blinker rechts Blinker zusammen Blinker links Masse
DauerPlus Batterie 12V (rot weiss) Ganganzeige Signal C (gelb weiss) Ganganzeige Signal B (gelb schwarz) Ganganzeige Signal A (gelb dunkelblau) 12V/350mA zum Starknopf (schwarz grün) Zündungsplus 12V (grün schwarz) Reservelampe (weiss) ABS Leuchte (blau) Ladekontrollleuchte (schaltet auf Masse) (vi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
Masse (braun) Lampentest (schaltet auf Masse)(weiss blau) Fernlichtlampe (12V) (weiss) Drehzahl Zündspule (schwarz blau) Blinker rechts (blau scharz) Masse (braun) Blinker links (blau rot) nicht angeschlossen Tachosiganl zum Blinrelais (balu grün) Tachogeber (gelb) Masse Tachobeger (braun) Tachobel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
4.7V
Stromquelle für Gang LEDs. Für mehr als 12mA muss ein Widerstand "R_user" eingelötet werden. Für weniger muss der 1kOhm SMD Widerstand neben R_user entfernt werden I = 12V/1kOhm(default)+12V/R_user I= 12mA (default) + 12V/R_user Beispiel: R_user Strom in LEDs 1 kOhm 22-26mA ohne 11-13mA
Gang 1
Gang 2
Gang 3
Gang 4
Gang 5
Variante "eine LED leuchtet"
Variante "alle LEDs bis und mit Gang X leuchten"
Klemmleisten Ausgang:
Klemmleisten Ausgang:
an Zündungsplus anhängen (Neutral leuchtet wenn Gang 0 eingelegt und Zündschlüssel steckt )
an Ausgang "Neutrallampe" anhängen
Neutrallampe für eigene Ganganzeige
Externe Beschaltung
Anzeige:
nicht bestückt
rising edge trigger A
BAR
RES
BL resistors
